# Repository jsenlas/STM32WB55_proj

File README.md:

# STM32WB55_proj

# Changelist
v01 
pred touto verziou boli len inicializacne commity
Zacal som minimalizaciu (susciastky blizsie a hustejsie), napriek tomu, ze este nemam spatnu vazbu, no je lepsie ked si prejdem umiestnenie a rozlozenie vsetkych suciastok.
Differential pair pre USB W0.341mm Separator0.2mm to by malo zarucit 90Ohm impedanciu.
Upratovanie Silkscreenu
Pridane 3d Modely .step subory

v02 8.3.2021
- otrasovane
- vyplnene plochy GND
- opravene vsetky chyby, ktore vznikali pri design rules checku
- pridanych par obrazkov, v ktorych je ulozene nastavenie pre niektore operacie, hlavne zony

v03 9.3.2021
- opravene RF trasy - zaoblenie, solder mask, vzdialenost vzhladom na dlzku anteny
- posunute USB dalej, aby som vytvoril priestor a napravil tak dalsie chyby kde sa mi prekryvali suciastky

ToDo:
- [] vyplnit priestor s vias na GND
- [] nepaci sa mi ako je poprepajane I2C (chaos) a USB (+ a - su prilis blizko pri sebe v USBLC6-2SC6)
- [x] doplnit "ohradu" z  GND vias okolo RF tras - nie je miesto

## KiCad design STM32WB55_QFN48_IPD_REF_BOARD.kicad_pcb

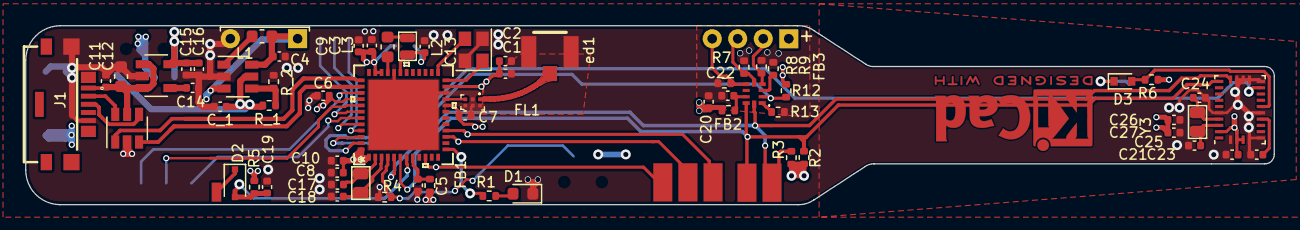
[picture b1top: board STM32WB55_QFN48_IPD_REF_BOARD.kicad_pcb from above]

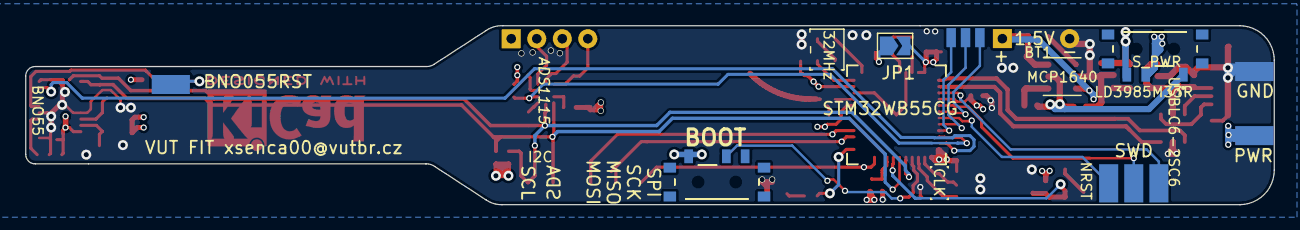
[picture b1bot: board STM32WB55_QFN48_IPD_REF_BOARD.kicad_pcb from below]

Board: 4 copper layers, 99.4 x 14.3 mm, 76 parts (8 on the bottom side), 52 nets.

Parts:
32MHz: NX2520SA-32MHz; Crystal_SMD_2520-4Pin_2.5x2.0mm
ADS1115: ADS1115IDGS; ADS1115IRUGR
BNO55: BNO055_my; LGA-28_5.2x3.8mm_P0.5mm
BNO055RST: Conn_01x01_Male; pin_01
BOOT: MLL1200S
BT1: Battery_Cell; battery_connector_narrow
C1, C5, C6, C7, C8, C9, C10, C15, C19, C21, C23, C26, C27: 100n; C_0402_1005Metric
C2: 100p; C_0402_1005Metric
C3, C4, C13: 4u7; C_0402_1005Metric
C11, C16, C20, C22: 1u; C_0402_1005Metric
C12: 100n; C_0603_1608Metric
C14: 10n; C_0402_1005Metric
C17, C18: 4p3; C_0402_1005Metric
C24, C25: 22p; C_0402_1005Metric
CLK: NX2012SA-32768K; Crystal_2012_custom
C_1: 10u; C_0402_1005Metric
D1: LED Blue; LED_0603_1608Metric
D2: BAT54J; D_SOD-323F
D3: 1N4148WT; D_SOD-523
FB1: BLM15AX601SN1D; R_0402_1005Metric
FB2, FB3: MMZ2012Y152BTD25; R_0402_1005Metric
FL1: MLPF-WB55-01E3; MLPF-WB55-02E3
GND: Conn_01x01_Male; pin_01
I2C: Conn_01x02_Male; pin_02
J1: USB_B_Micro; UB-MC5BR3-SDWP604-4S-TF
J4: Conn_01x04_Male; Pin_FSR
JP1: SolderJumper Open; SolderJumper-2_P1.3mm_Open_TrianglePad1.0x1.5mm
J_GEN1: Conn_01x03_Male; pin_03
J_SPI1: Conn_01x03_Male; pin_03
L1: 4u7; L_0603_1608Metric
L2: 10u; L_0712_SMD
L3: 10n; L_0603_1608Metric
LD3985M33R: LD3985M33R; SOT-23-5
MCP1640: MCP1640CCH; SOT-23-6
N1: Housing; KiCad-Logo2_5mm_Copper
NRST: Conn_01x01_Male; pin_01
PWR: Conn_01x01_Male; pin_01
R1, R5, R7, R8, R9: 100K; R_0402_1005Metric
R2, R3, R4, R6, R12, R13: 10K; R_0402_1005Metric
R_1: 976k; R_0402_1005Metric
R_2: 562k; R_0402_1005Metric
SWD: Conn_01x03_Male; pin_03
S_PWR: MLL1200S
U2: STM32WB55CG; STM32WB55CGU7
USBLC6-2SC6: USBLC6-2SC6; SOT-23-6
Y3: NX2012SA-32768K; Crystal_2012_custom
ed1: RECE.20279.001E.01

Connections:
3v3fromBAT: C_1.1, MCP1640.5, R_1.1, S_PWR.1
3v3fromUSB: C15.1, C16.1, LD3985M33R.5, S_PWR.3
+1V5: BT1.1, C4.1, L1.1, MCP1640.3, MCP1640.6
+3V3: BNO55.3, BNO55.4, BNO55.28, BOOT.1, C1.1, C2.1, C3.1, C6.1, C7.1, C8.1, C9.1, C10.1, C20.2, C21.1, C26.1, C27.1, FB1.1, FB2.1, J4.1, JP1.2, PWR.1, R2.1, R3.1, R5.1, R6.1, R12.1, S_PWR.2, U2.1, U2.20, U2.23, U2.34, U2.35, U2.40, U2.48
+5V: C11.1, C12.1, J1.1, LD3985M33R.1, LD3985M33R.3, USBLC6-2SC6.5
/R_OUT: FL1.1, ed1.3
ADC_ALERT: ADS1115.2, R12.2, U2.46
BNO055_INT: BNO55.14, U2.47
BNO055_RESET: BNO055RST.1, D3.1
GENERAL_PIN_OUT1: J_GEN1.1, U2.42
GENERAL_PIN_OUT2: J_GEN1.2, U2.44
GENERAL_PIN_OUT3: J_GEN1.3, U2.45
GND: 32MHz.2, 32MHz.4, BNO55.2, BNO55.5, BNO55.6, BNO55.10, BNO55.15, BNO55.16, BNO55.17, BNO55.18, BNO55.25, BT1.2, C1.2, C2.2, C3.2, C4.2, C5.2, C6.2, C7.2, C8.2, C9.2, C10.2, C11.2, C12.2, C13.2, C14.2, C15.2, C16.2, C17.2, C18.2, C19.2, C20.1, C21.2, C22.1, C23.2, C24.2, C25.2, C26.2, C27.2, C_1.2, D1.1, FB3.2, FL1.2, FL1.4, FL1.5, FL1.6, GND.1, J1.5, J1.6, LD3985M33R.2, MCP1640.2, R4.2, R7.2, R8.2, R9.2, R13.2, R_2.2, U2.22, U2.32, U2.49, USBLC6-2SC6.2, ed1.1, ed1.2
I2C_SCL: ADS1115.10, BNO55.19, I2C.1, R3.2, U2.5
I2C_SDA: ADS1115.9, BNO55.20, I2C.2, R2.2, U2.6
LED_BLUE: R1.1, U2.13
NRST: D2.1, NRST.1
unnamed: ADS1115.1, R13.1
unnamed: ADS1115.3, FB3.1
unnamed: ADS1115.4, J4.2, R9.1
unnamed: ADS1115.5, J4.3, R8.1
unnamed: ADS1115.6, J4.4, R7.1
unnamed: ADS1115.8, C22.2, FB2.2
unnamed: BNO55.9, C23.1
unnamed: BNO55.11, D3.2, R6.2
unnamed: BNO55.26, C24.1, Y3.1
unnamed: BNO55.27, C25.1, Y3.2
unnamed: C5.1, FB1.2, U2.8
unnamed: C13.1, JP1.1, L2.1, U2.31
unnamed: C14.1, LD3985M33R.4
unnamed: C17.1, CLK.2, U2.2
unnamed: C18.1, CLK.1, U2.3
unnamed: C19.1, D2.2, R5.2, U2.7
unnamed: D1.2, R1.2
unnamed: L1.2, MCP1640.1
unnamed: L2.2, L3.1
unnamed: L3.2, U2.33
unnamed: MCP1640.4, R_1.2, R_2.1
unnamed: BOOT.2, R4.1, U2.4
unnamed: 32MHz.1, U2.24
unnamed: 32MHz.3, U2.25
RF1: FL1.3, U2.21
SPI_MISO: J_SPI1.2, U2.15
SPI_MOSI: J_SPI1.1, U2.16
SPI_SCK: J_SPI1.3, U2.10
SYS_JTCK-SWCLK: SWD.2, U2.41
SYS_JTDO-SWO: SWD.3, U2.43
SYS_JTMS-SWDIO: SWD.1, U2.39
USB_D+: U2.38, USBLC6-2SC6.3
USB_D-: U2.37, USBLC6-2SC6.1
USB_OD+: J1.3, USBLC6-2SC6.4
USB_OD-: J1.2, USBLC6-2SC6.6

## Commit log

2021-03-03 init
2021-03-03 solved issues from init
2021-03-03 added files to pack in Makefile

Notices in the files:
parts and their libraries:
Copyright 2016 Accelerated Designs. All rights reserved.
